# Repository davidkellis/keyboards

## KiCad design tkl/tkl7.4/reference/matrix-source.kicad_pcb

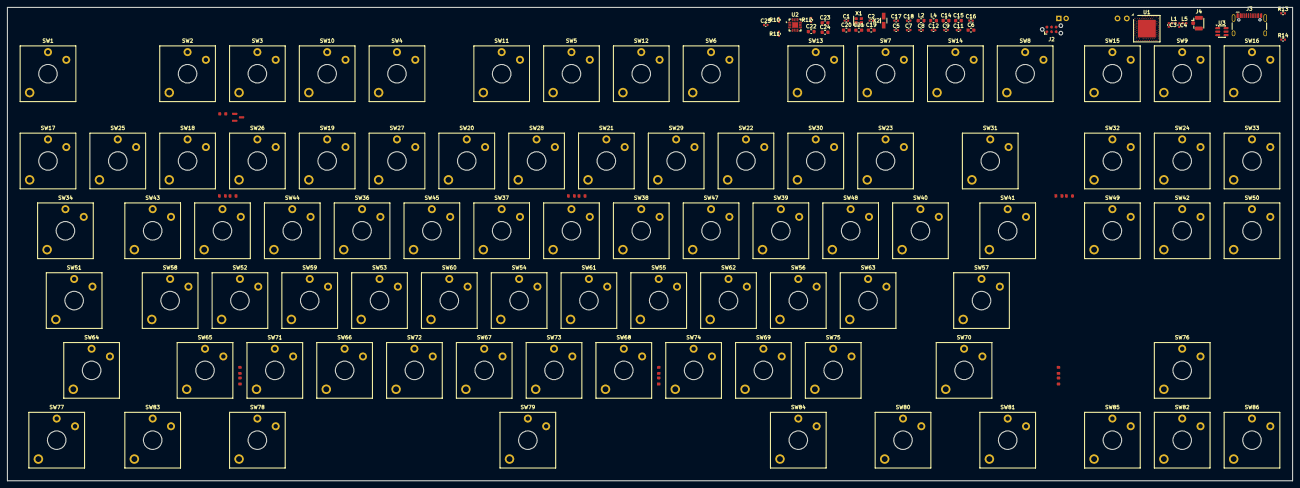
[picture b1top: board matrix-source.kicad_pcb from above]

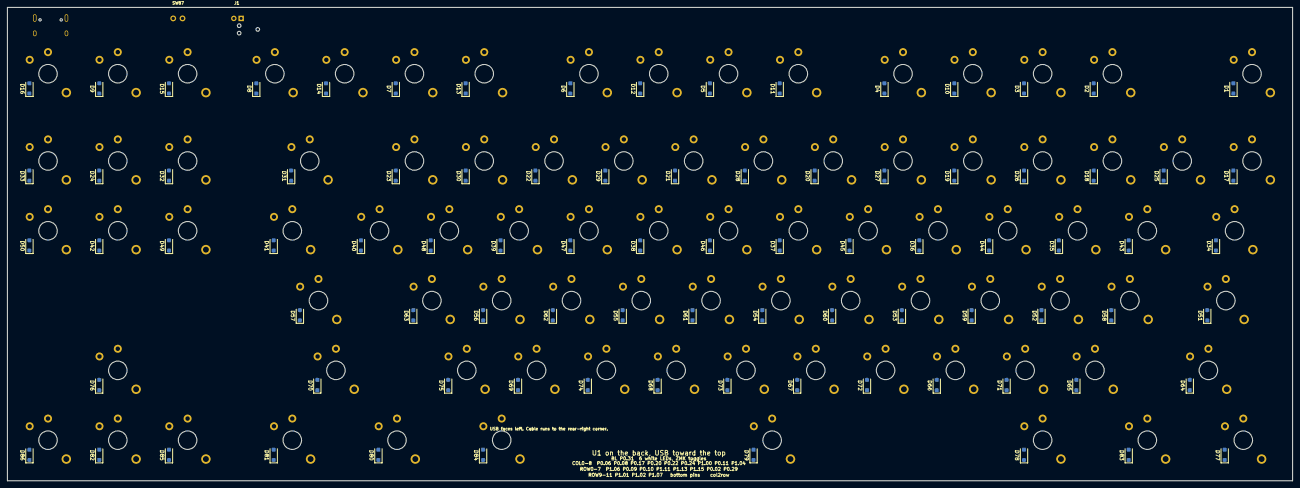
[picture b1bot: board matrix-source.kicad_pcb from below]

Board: 2 copper layers, 350.8 x 129.2 mm, 228 parts (88 on the bottom side), 145 nets, no tracks yet.

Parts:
C1, C2, C17, C18: 12pF; C_0402_1005Metric
C3: 1.0pF; C_0402_1005Metric
C4: 1.2pF; C_0402_1005Metric
C5, C7, C8, C12: 100nF; C_0402_1005Metric
C6, C19, C20, C21, C23, C24: 4.7uF; C_0603_1608Metric
C9: 820pF; C_0402_1005Metric
C11: 100pF; C_0402_1005Metric
C14, C15, C22: 1uF; C_0603_1608Metric
C16, C25: 47nF; C_0402_1005Metric
D1, D2, D3, D4, D5, D6, D7, D8, D9, D10, D11, D12, D13, D14, D15, D16, D17, D18, D19, D20, D21, D22, D23, D24, D25, D26, D27, D28, D29, D30, D31, D32, D33, D34, D35, D36, D37, D38, D39, D40, D41, D42, D43, D44, D45, D46, D47, D48, D49, D50, D51, D52, D53, D54, D55, D56, D57, D58, D59, D60, D61, D62, D63, D64, D65, D66, D67, D68, D69, D70, D71, D72, D73, D74, D75, D76, D77, D78, D79, D80, D81, D82, D83, D84, D85, D86: D; D_SOD-123F
J1: BAT; JST_PH_2
J2: Tag-Connect_TC2030-IDC-NL_2x03_P1.27mm_Vertical
J3: USB-C; USB_C_Receptacle_HCTL_HC-TYPE-C-16P-01A
J4: IPX; U.FL_Hirose_U.FL-R-SMT-1_Vertical
L1: 4.7nH; L_0402_1005Metric
L2, L4: 10uH; L_0603_1608Metric
L5: 2.2nH; L_0402_1005Metric
LED1, LED3, LED4: White; LED_0603
LED2, LED5, LED6: White; LED_0603_270
Q1: AO3400; SOT-23
R1, R3, R4: 560; R_0603
R2, R5, R6: 560; R_0603_270
R9: 100k; R_0603
R10: 10k; R_0402_1005Metric
R11: 1.78k; R_0402_1005Metric
R12: 1.13k; R_0402_1005Metric
R13, R14: 5.1k; R_0402_1005Metric
SW1, SW2, SW3, SW4, SW5, SW6, SW7, SW8, SW9, SW10, SW11, SW12, SW13, SW14, SW15, SW16, SW17, SW18, SW19, SW20, SW21, SW22, SW23, SW24, SW25, SW26, SW27, SW28, SW29, SW30, SW32, SW33, SW35, SW36, SW37, SW38, SW39, SW40, SW42, SW43, SW44, SW45, SW46, SW47, SW48, SW49, SW50, SW52, SW53, SW54, SW55, SW56, SW58, SW59, SW60, SW61, SW62, SW63, SW65, SW66, SW67, SW68, SW69, SW71, SW72, SW73, SW74, SW75, SW76, SW82, SW85, SW86: SW_Push; SW_Kailh_Choc_V2_1.00u
SW31: SW_Push; SW_Kailh_Choc_V2_2.00u
SW34, SW41, SW78, SW80, SW81, SW83, SW84: SW_Push; SW_Kailh_Choc_V2_1.50u
SW51: SW_Push; SW_Kailh_Choc_V2_1.75u
SW57, SW64: SW_Push; SW_Kailh_Choc_V2_2.25u
SW70: SW_Push; SW_Kailh_Choc_V2_2.75u
SW77: SW_Push; SW_Kailh_Choc_V2_1.25u
SW79: SW_Push; SW_Kailh_Choc_V2_6.25u
SW87: PWR; SW_SLIDE
U1: Nordic_AQFN-73-1EP_7x7mm_P0.5mm
U2: BQ24072; VQFN-16-1EP_3x3mm_P0.5mm_EP1.6x1.6mm
U3: USBLC6-2SC6; SOT-23-6
X1: 32MHz; Crystal_SMD_2016-4Pin_2.0x1.6mm
X2: 32.768kHz; Crystal_SMD_3215-2Pin_3.2x1.5mm

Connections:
ANT: C3.1, L1.1, U1.H23
ANT_CONN: J4.1, L5.2
BAT+: J1.1, SW87.1
BL: LED1.1, LED2.1, LED3.1, LED4.1, LED5.1, LED6.1, Q1.3
BL_EN: Q1.1, R9.1, U1.A8
COL0: SW1.1, SW17.1, SW25.1, SW34.1, SW43.1, SW51.1, SW58.1, SW64.1, SW77.1, SW83.1, U1.L1
COL1: SW2.1, SW18.1, SW26.1, SW35.1, SW44.1, SW52.1, SW59.1, SW65.1, SW71.1, SW78.1, U1.N1
COL2: SW3.1, SW10.1, SW19.1, SW27.1, SW36.1, SW45.1, SW53.1, SW60.1, SW66.1, SW72.1, U1.AD12
COL3: SW4.1, SW11.1, SW20.1, SW28.1, SW37.1, SW46.1, SW54.1, SW61.1, SW67.1, SW73.1, SW79.1, U1.AD16
COL4: SW5.1, SW12.1, SW21.1, SW29.1, SW38.1, SW47.1, SW55.1, SW62.1, SW68.1, SW74.1, U1.AD18
COL5: SW6.1, SW13.1, SW22.1, SW30.1, SW39.1, SW48.1, SW56.1, SW63.1, SW69.1, SW75.1, SW84.1, U1.AD20
COL6: SW7.1, SW14.1, SW23.1, SW31.1, SW40.1, SW57.1, SW70.1, SW80.1, U1.AD22
COL7: SW8.1, SW15.1, SW32.1, SW41.1, SW49.1, SW81.1, SW85.1, U1.T2
COL8: SW9.1, SW16.1, SW24.1, SW33.1, SW42.1, SW50.1, SW76.1, SW82.1, SW86.1, U1.U24
DCC: L4.1, U1.B3
DCCH: C14.1, L2.2, U1.AB2
DEC1: C12.1, U1.C1
DEC2: C5.1, U1.A18, U1.E24
DEC4: C16.1, L4.2, U1.B5
DEC5: C9.1, U1.N24
DECUSB: C6.1, C11.1, U1.AC5
GND: C1.2, C2.2, C3.2, C4.2, C5.2, C6.2, C7.2, C8.2, C9.2, C11.2, C12.2, C14.2, C15.2, C16.2, C17.2, C18.2, C19.2, C20.2, C21.2, C22.2, C23.2, C24.2, C25.2, J1.2, J2.5, J3.A1, J3.A12, J3.B1, J3.B12, J4.2, Q1.2, R9.2, R10.2, R11.2, R12.2, R13.2, R14.2, U1.B7, U1.EP, U1.F23, U2.4, U2.6, U2.8, U2.15, U2.17, U3.2, X1.2, X1.4
ILIM: R12.1, U2.12
ISET: R11.1, U2.16
unnamed: D1.2 (A), SW1.2
unnamed: D2.2 (A), SW2.2
unnamed: D3.2 (A), SW3.2
unnamed: D4.2 (A), SW4.2
unnamed: D5.2 (A), SW5.2
unnamed: D6.2 (A), SW6.2
unnamed: D7.2 (A), SW7.2
unnamed: D8.2 (A), SW8.2
unnamed: D9.2 (A), SW9.2
unnamed: D10.2 (A), SW10.2
unnamed: D11.2 (A), SW11.2
unnamed: D12.2 (A), SW12.2
unnamed: D13.2 (A), SW13.2
unnamed: D14.2 (A), SW14.2
unnamed: D15.2 (A), SW15.2
unnamed: D16.2 (A), SW16.2
unnamed: D17.2 (A), SW17.2
unnamed: D18.2 (A), SW18.2
unnamed: D19.2 (A), SW19.2
unnamed: D20.2 (A), SW20.2
unnamed: D21.2 (A), SW21.2
unnamed: D22.2 (A), SW22.2
unnamed: D23.2 (A), SW23.2
unnamed: D24.2 (A), SW24.2
unnamed: D25.2 (A), SW25.2
unnamed: D26.2 (A), SW26.2
unnamed: D27.2 (A), SW27.2
unnamed: D28.2 (A), SW28.2
unnamed: D29.2 (A), SW29.2
unnamed: D30.2 (A), SW30.2
unnamed: D31.2 (A), SW31.2
unnamed: D32.2 (A), SW32.2
unnamed: D33.2 (A), SW33.2
unnamed: D34.2 (A), SW34.2
unnamed: D35.2 (A), SW35.2
unnamed: D36.2 (A), SW36.2
unnamed: D37.2 (A), SW37.2
unnamed: D38.2 (A), SW38.2
unnamed: D39.2 (A), SW39.2
unnamed: D40.2 (A), SW40.2
unnamed: D41.2 (A), SW41.2
unnamed: D42.2 (A), SW42.2
unnamed: D43.2 (A), SW43.2
unnamed: D44.2 (A), SW44.2
unnamed: D45.2 (A), SW45.2
unnamed: D46.2 (A), SW46.2
unnamed: D47.2 (A), SW47.2
unnamed: D48.2 (A), SW48.2
unnamed: D49.2 (A), SW49.2
unnamed: D50.2 (A), SW50.2
unnamed: D51.2 (A), SW51.2
unnamed: D52.2 (A), SW52.2
unnamed: D53.2 (A), SW53.2
unnamed: D54.2 (A), SW54.2
unnamed: D55.2 (A), SW55.2
unnamed: D56.2 (A), SW56.2
unnamed: D57.2 (A), SW57.2
unnamed: D58.2 (A), SW58.2
unnamed: D59.2 (A), SW59.2
unnamed: D60.2 (A), SW60.2
unnamed: D61.2 (A), SW61.2
unnamed: D62.2 (A), SW62.2
unnamed: D63.2 (A), SW63.2
unnamed: D64.2 (A), SW64.2
unnamed: D65.2 (A), SW65.2
unnamed: D66.2 (A), SW66.2
unnamed: D67.2 (A), SW67.2
unnamed: D68.2 (A), SW68.2
unnamed: D69.2 (A), SW69.2
unnamed: D70.2 (A), SW70.2
unnamed: D71.2 (A), SW71.2
unnamed: D72.2 (A), SW72.2
unnamed: D73.2 (A), SW73.2
unnamed: D74.2 (A), SW74.2
unnamed: D75.2 (A), SW75.2
unnamed: D76.2 (A), SW76.2
unnamed: D77.2 (A), SW77.2
unnamed: D78.2 (A), SW78.2
unnamed: D79.2 (A), SW79.2
unnamed: D80.2 (A), SW80.2
unnamed: D81.2 (A), SW81.2
unnamed: D82.2 (A), SW82.2
unnamed: D83.2 (A), SW83.2
unnamed: D84.2 (A), SW84.2
unnamed: D85.2 (A), SW85.2
unnamed: D86.2 (A), SW86.2
RESET: J2.3, U1.AC13
RF2: C4.1, L1.2, L5.1
ROW0: D1.1 (K), D2.1 (K), D3.1 (K), D4.1 (K), D5.1 (K), D6.1 (K), D7.1 (K), D8.1 (K), D9.1 (K), U1.R24
ROW1: D10.1 (K), D11.1 (K), D12.1 (K), D13.1 (K), D14.1 (K), D15.1 (K), D16.1 (K), U1.L24
ROW2: D17.1 (K), D18.1 (K), D19.1 (K), D20.1 (K), D21.1 (K), D22.1 (K), D23.1 (K), D24.1 (K), U1.J24
ROW3: D25.1 (K), D26.1 (K), D27.1 (K), D28.1 (K), D29.1 (K), D30.1 (K), D31.1 (K), D32.1 (K), D33.1 (K), U1.B19
ROW4: D34.1 (K), D35.1 (K), D36.1 (K), D37.1 (K), D38.1 (K), D39.1 (K), D40.1 (K), D41.1 (K), D42.1 (K), U1.A16
ROW5: D43.1 (K), D44.1 (K), D45.1 (K), D46.1 (K), D47.1 (K), D48.1 (K), D49.1 (K), D50.1 (K), U1.A14
ROW6: D51.1 (K), D52.1 (K), D53.1 (K), D54.1 (K), D55.1 (K), D56.1 (K), D57.1 (K), U1.A12
ROW7: D58.1 (K), D59.1 (K), D60.1 (K), D61.1 (K), D62.1 (K), D63.1 (K), U1.A10
ROW9: D64.1 (K), D70.1 (K), D71.1 (K), D72.1 (K), D73.1 (K), D74.1 (K), D75.1 (K), D76.1 (K), U1.Y23
ROW10: D66.1 (K), D68.1 (K), D69.1 (K), D77.1 (K), D78.1 (K), D79.1 (K), D80.1 (K), D81.1 (K), D82.1 (K), U1.W24
ROW11: D65.1 (K), D67.1 (K), D83.1 (K), D84.1 (K), D85.1 (K), D86.1 (K), U1.P23
S1: LED1.2, R1.1
S2: LED2.2, R2.1
S3: LED3.2, R3.1
S4: LED4.2, R4.1
S5: LED5.2, R5.1
S6: LED6.2, R6.1
SWCLK: J2.4, U1.AA24
SWDIO: J2.2, U1.AC24
TMR: C25.1, U2.14
TS: R10.1, U2.1
USB_CC1: J3.A5, R13.1
USB_CC2: J3.B5, R14.1
USB_DM: J3.A7, J3.B7, U1.AD4, U3.3, U3.4
USB_DP: J3.A6, J3.B6, U1.AD6, U3.1, U3.6
VBAT: C24.1, SW87.2, U2.2, U2.3
VBUS: C22.1, J3.A4, J3.A9, J3.B4, J3.B9, U1.AD2, U2.13, U3.5
VDD: C7.1, C8.1, C19.1, C20.1, C21.1, J2.1, R1.2, R2.2, R3.2, R4.2, R5.2, R6.2, U1.A22, U1.AD14, U1.AD23, U1.B1, U1.D23, U1.W1
VDDH: C15.1, C23.1, L2.1, U1.Y2, U2.5, U2.10, U2.11
XC1: C1.1, U1.B24, X1.1
XC2: C2.1, U1.A23, X1.3
XL1: C17.1, U1.D2, X2.1
XL2: C18.1, U1.F2, X2.2
